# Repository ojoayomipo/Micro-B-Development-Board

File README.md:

# Micro-B-Development-Board
The Micro-B development board is based on the ATMEGA328 microcontroller. It is an all-in-one board to help engineers take on several beginner and intermediate projects in embedded systems with the components all in one place.With this in place, they can do rapid PoCs with ease.
This repository contains the KICAD schematics and PCB designs.

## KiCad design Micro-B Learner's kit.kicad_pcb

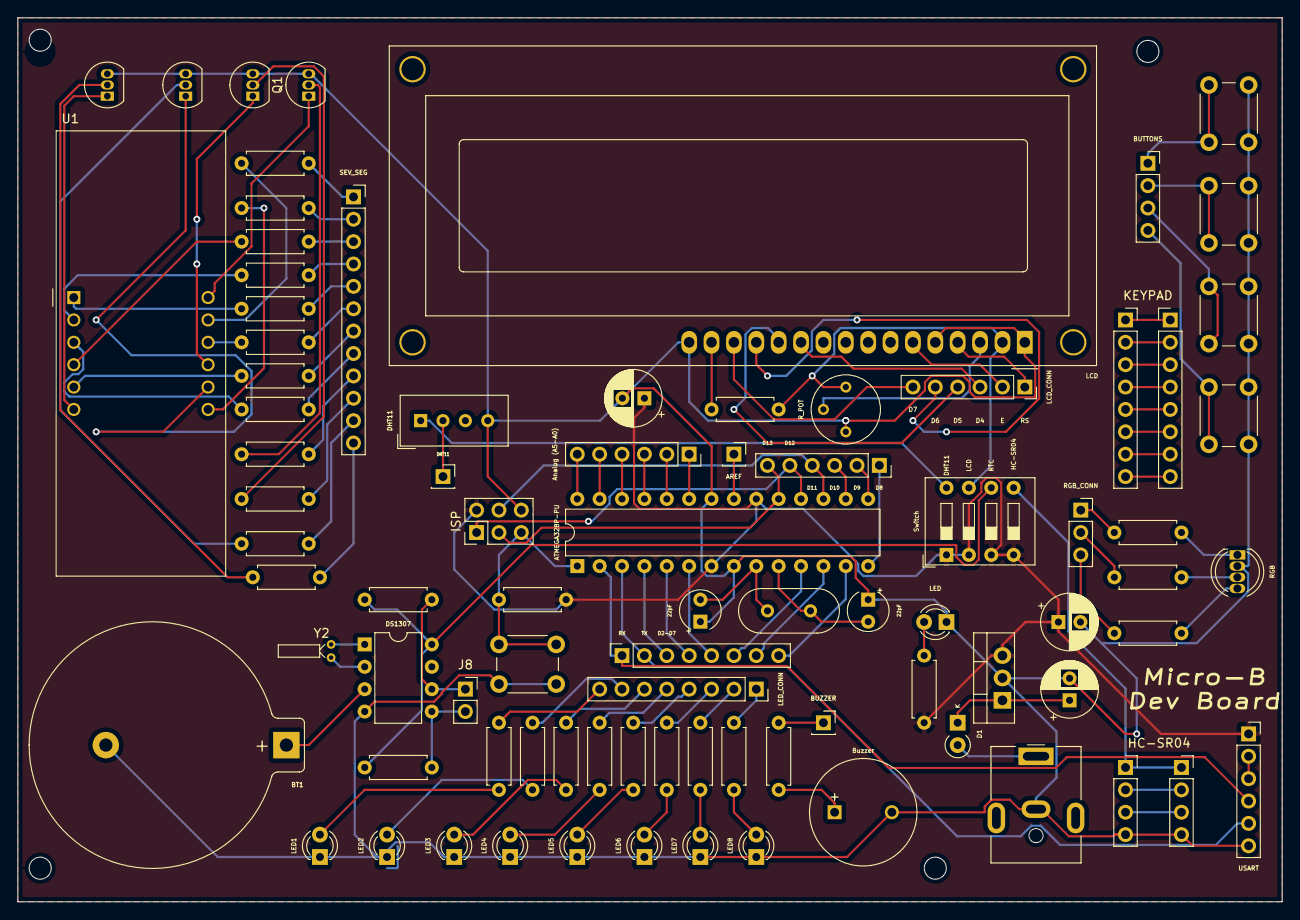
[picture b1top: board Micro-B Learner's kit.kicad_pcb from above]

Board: 2 copper layers, 143.5 x 100.3 mm, 85 parts (0 on the bottom side), 114 nets.

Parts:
22pF, 22pF#2: 22pF; CP_Radial_Tantal_D4.5mm_P2.50mm
AREF: AREF; PinSocket_1x01_P2.54mm_Vertical
ATMEGA328P-PU: ATmega328P-PU; DIP-28_W7.62mm
Analog (A5-A0): ANALOG; PinSocket_1x06_P2.54mm_Vertical
BT1: Battery; BatteryHolder_Keystone_107_1x23mm
BUTTONS: BUTTONS; PinSocket_1x04_P2.54mm_Vertical
BUZZER: BUZ_CONN; PinSocket_1x01_P2.54mm_Vertical
Buzzer: Buzzer; MagneticBuzzer_ProSignal_ABT-410-RC
C3, C4, C5: CP1_Small; CP_Radial_D6.3mm_P2.50mm
D1: D_Schottky_Small_ALT; D_A-405_P2.54mm_Vertical_KathodeUp
DHT11: DHT11; Aosong_DHT11_5.5x12.0_P2.54mm
DHT11#2: DHT11_CONN; PinSocket_1x01_P2.54mm_Vertical
DS1307: DS1307+; DIP-8_W7.62mm
HC-SR04: HC-SR04; PinSocket_1x04_P2.54mm_Vertical
ISP: AVR-ISP-6; PinHeader_2x03_P2.54mm_Vertical
J1: Barrel_Jack; BarrelJack_CUI_PJ-063AH_Horizontal
J8: Conn_01x02; PinSocket_1x02_P2.54mm_Vertical
J11: HC-SR04; PinSocket_1x04_P2.54mm_Vertical
J12: D7-D13; PinSocket_1x06_P2.54mm_Vertical
J14: D0-D7; PinSocket_1x08_P2.54mm_Vertical
J19: KEYPAD; PinHeader_1x08_P2.54mm_Vertical
KEYPAD: KEYPAD; PinSocket_1x08_P2.54mm_Vertical
LCD: RC1602A; WC1602A
LCD_CONN: LCD_CONN; PinSocket_1x06_P2.54mm_Vertical
LED, LED1, LED2, LED3, LED4, LED5, LED6, LED7, LED8: LED_ALT; LED_D3.0mm_Clear
LED_CONN: LED; PinSocket_1x08_P2.54mm_Vertical
Q1, Q2, Q3, Q4: BC547; TO-92_Inline
R1: 10k; R_Axial_DIN0207_L6.3mm_D2.5mm_P7.62mm_Horizontal
R2, R3, R4, R5, R6, R7, R8, R9, R10, R11, R12, R13, R14, R15, R16, R17, R18, R19, R20, R21, R22, R23, R24, R25, R26, R27, R28, R29: R_Small; R_Axial_DIN0207_L6.3mm_D2.5mm_P7.62mm_Horizontal
RGB: LED_RCGB; LED_D5.0mm-4_RGB
RGB_CONN: RGB_CONN; PinSocket_1x03_P2.54mm_Vertical
R_POT: R_POT; Potentiometer_Bourns_3339P_Vertical
SEV_SEG: SEV_SEG; PinSocket_1x12_P2.54mm_Vertical
SW1: RESET_BUTTON; SW_PUSH_6mm_H4.3mm
SW3, SW4, SW5, SW6: SW_Push; SW_PUSH_6mm_H4.3mm
Switch: SW_DIP_x04; SW_DIP_SPSTx04_Slide_9.78x12.34mm_W7.62mm_P2.54mm
U1: CC56-12EWA; CA56-12EWA
U2: LM7805_TO220; TO-220-3_Vertical
USART: USART; PinSocket_1x06_P2.54mm_Vertical
Y1: Crystal; Crystal_HC49-4H_Vertical
Y2: Crystal; Crystal_DS10_D1.0mm_L4.3mm_Horizontal

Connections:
5V: ATMEGA328P-PU.7, ATMEGA328P-PU.20, C4.1, C5.1, ISP.2, R1.2, R2.2, Switch.1, Switch.2, Switch.3, Switch.4, U2.3, USART.1
A0: ATMEGA328P-PU.23, Analog (A5-A0).1
A1: ATMEGA328P-PU.24, Analog (A5-A0).2
A2: ATMEGA328P-PU.25, Analog (A5-A0).3
A3: ATMEGA328P-PU.26, Analog (A5-A0).4
A4: ATMEGA328P-PU.27, Analog (A5-A0).5
A5: ATMEGA328P-PU.28, Analog (A5-A0).6
D2: ATMEGA328P-PU.4, J14.3
D3: ATMEGA328P-PU.5, J14.4
D4: ATMEGA328P-PU.6, J14.5
D5: ATMEGA328P-PU.11, J14.6
D6: ATMEGA328P-PU.12, J14.7
D7: ATMEGA328P-PU.13, J14.8
D8: ATMEGA328P-PU.14, J12.1
D9: ATMEGA328P-PU.15, J12.2
D10: ATMEGA328P-PU.16, J12.3
D11: ATMEGA328P-PU.17, ISP.4, J12.4
D12: ATMEGA328P-PU.18, ISP.1, J12.5
D13: ATMEGA328P-PU.19, ISP.3, J12.6
DHT11: DHT11.1, Switch.8
GND: 22pF.1, 22pF#2.1, ATMEGA328P-PU.8, ATMEGA328P-PU.22, BT1.2, Buzzer.2, C3.2, C4.2, C5.2, DHT11.4, DS1307.4, HC-SR04.4, ISP.6, J1.2, J11.4, LCD.1, LCD.5, LCD.16, LED.1, LED1.1, LED2.1, LED3.1, LED4.1, LED5.1, LED6.1, LED7.1, LED8.1, Q1.3, Q2.3, Q3.3, Q4.3, RGB.2, R_POT.1, SW1.2, SW3.1, SW4.1, SW5.1, SW6.1, U2.2, USART.6
HC-SR04: HC-SR04.1, J11.1, Switch.5
LCD: LCD.2, R7.1, R_POT.3, Switch.7
unnamed: BT1.1, DS1307.3
unnamed: Buzzer.1, R27.1
unnamed: C3.1, D1.1, U2.1
unnamed: D1.2, J1.1
unnamed: LED.2, R2.1
unnamed: R4.2, RGB.1
unnamed: R5.2, RGB.3
unnamed: R6.2, RGB.4
unnamed: LED2.2, R28.1
unnamed: LED8.2, R8.1
unnamed: LED7.2, R9.1
unnamed: LED6.2, R10.1
unnamed: LED5.2, R11.1
unnamed: LED4.2, R12.1
unnamed: LED3.2, R13.1
unnamed: LED1.2, R29.1
unnamed: R4.1, RGB_CONN.1
unnamed: R5.1, RGB_CONN.2
unnamed: R6.1, RGB_CONN.3
unnamed: LCD.4, LCD_CONN.1
unnamed: LCD.6, LCD_CONN.2
unnamed: LCD.11, LCD_CONN.3
unnamed: LCD.12, LCD_CONN.4
unnamed: LCD.13, LCD_CONN.5
unnamed: LCD.14, LCD_CONN.6
unnamed: DHT11.2, DHT11#2.1
unnamed: LED_CONN.1, R8.2
unnamed: LED_CONN.2, R9.2
unnamed: LED_CONN.3, R10.2
unnamed: LED_CONN.4, R11.2
unnamed: LED_CONN.5, R12.2
unnamed: LED_CONN.6, R13.2
unnamed: LED_CONN.7, R28.2
unnamed: LED_CONN.8, R29.2
unnamed: R3.1, SEV_SEG.1
unnamed: R14.1, SEV_SEG.2
unnamed: R15.1, SEV_SEG.3
unnamed: R16.1, SEV_SEG.4
unnamed: R17.1, SEV_SEG.5
unnamed: R18.1, SEV_SEG.6
unnamed: R19.1, SEV_SEG.7
unnamed: R20.1, SEV_SEG.8
unnamed: R21.2, SEV_SEG.9
unnamed: R22.2, SEV_SEG.10
unnamed: R23.2, SEV_SEG.11
unnamed: R24.2, SEV_SEG.12
unnamed: BUZZER.1, R27.2
unnamed: DS1307.6, J8.1, R25.2
unnamed: DS1307.5, J8.2, R26.2
unnamed: BUTTONS.1, SW3.2
unnamed: BUTTONS.2, SW4.2
unnamed: BUTTONS.3, SW5.2
unnamed: BUTTONS.4, SW6.2
unnamed: HC-SR04.2, J11.2
unnamed: HC-SR04.3, J11.3
unnamed: AREF.1, ATMEGA328P-PU.21
unnamed: USART.2, USART.3
unnamed: J19.1, KEYPAD.1
unnamed: J19.2, KEYPAD.2
unnamed: J19.3, KEYPAD.3
unnamed: J19.4, KEYPAD.4
unnamed: J19.5, KEYPAD.5
unnamed: J19.6, KEYPAD.6
unnamed: J19.7, KEYPAD.7
unnamed: J19.8, KEYPAD.8
unnamed: Q1.1, U1.12
unnamed: Q1.2, R21.1
unnamed: Q2.1, U1.9
unnamed: Q2.2, R22.1
unnamed: Q3.1, U1.8
unnamed: Q3.2, R23.1
unnamed: Q4.1, U1.6
unnamed: Q4.2, R24.1
unnamed: R3.2, U1.11
unnamed: LCD.15, R7.2
unnamed: R14.2, U1.7
unnamed: R15.2, U1.4
unnamed: R16.2, U1.2
unnamed: R17.2, U1.1
unnamed: R18.2, U1.10
unnamed: R19.2, U1.5
unnamed: R20.2, U1.3
unnamed: LCD.3, R_POT.2
unnamed: DS1307.1, Y2.1
unnamed: DS1307.2, Y2.2
RESET: ATMEGA328P-PU.1, ISP.5, R1.1, SW1.1
RTC: DS1307.8, R25.1, R26.1, Switch.6
RX: ATMEGA328P-PU.2, J14.1, USART.4
TX: ATMEGA328P-PU.3, J14.2, USART.5
XTAL1: 22pF#2.2, ATMEGA328P-PU.9, Y1.1
XTAL2: 22pF.2, ATMEGA328P-PU.10, Y1.2
